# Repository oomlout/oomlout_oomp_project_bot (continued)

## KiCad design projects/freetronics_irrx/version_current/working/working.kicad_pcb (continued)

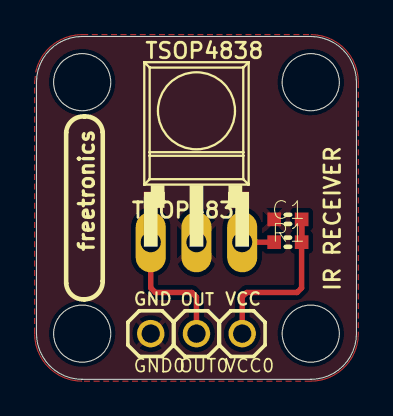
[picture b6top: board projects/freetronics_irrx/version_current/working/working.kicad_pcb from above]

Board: 2 copper layers, 17.8 x 19.0 mm, 10 parts (0 on the bottom side), 4 nets.

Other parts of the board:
@HOLE0, @HOLE1, @HOLE2, @HOLE3: (no value)

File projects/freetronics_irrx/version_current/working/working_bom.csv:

"Id";"Designator";"Footprint";"Quantity";"Designation";"Supplier and ref";
1;"R1";"0603";1;"100R";;;
2;"@HOLE3,@HOLE0,@HOLE1,@HOLE2";"";4;"";;;
3;"C1";"0603";1;"0.1u";;;
4;"VCC0,GND0,OUT0";"1X01";3;"M01PTH";;;
5;"TSOP4838";"TO220";1;"TSOP4838";;;

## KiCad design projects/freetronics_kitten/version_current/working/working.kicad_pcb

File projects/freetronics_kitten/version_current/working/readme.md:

# OOMP Project  
## KitTen  by freetronics  
  
oomp key: oomp_projects_flat_freetronics_kitten  
(snippet of original readme)  
  
Freetronics KitTen  
==================  
Copyright 2010-2013 Freetronics Pty Ltd    
Freetronics site:  www.freetronics.com    
Freetronics email: info@freetronics.com    
  
A fully-featured Arduino-compatible board in kit form. Includes a  
voltage regulator and extensive filtering, plus a prototyping area.  
  
Features:  
  
 * Prototyping area  
 * Overlay guide where you need it (both top and bottom)  
 * D13 pin works for everything thanks to FET isolation  
 * RX pin biased  
 * Mounting holes and power pads  
 * R3 (revision 3) Arduino header format  
  
More information is available at:  
  
  http://www.freetronics.com/kitten  

INSTALLATION  
------------  
The design is saved as an EAGLE project. EAGLE PCB design software is  
available from www.cadsoftusa.com free for non-commercial use. To use  
this project download it and place the directory containing these files  
into the "eagle" directory on your computer. Then open EAGLE and  
navigate to Projects -> eagle -> KitTen.  

DISTRIBUTION  
------------  
The specific terms of distribution of this project are governed by the  
license referenced below.  

LICENSE  
-------  
This work is licensed under the  
Creative Commons Attribution-Share Alike License.    
To view a copy of this license, visit  
  
  http://creativecommons.org/licenses/by-sa/3.0/    
  http://creativecommons.org/licenses/by-sa/3.0/legalcode  
  
or send a letter to  
  
  Creative Commons    
  171 Second Street, Suite 300    
  San Francisco    
  California, 94105    
  USA  
  
The "license" folder within this repository also c  
  full source readme at [readme_src.md](readme_src.md)  
  
source repo at: [https://github.com/freetronics/KitTen](https://github.com/freetronics/KitTen)  
## Board  

## Schematic  

[schematic pdf](working_schematic.pdf)  
## Images

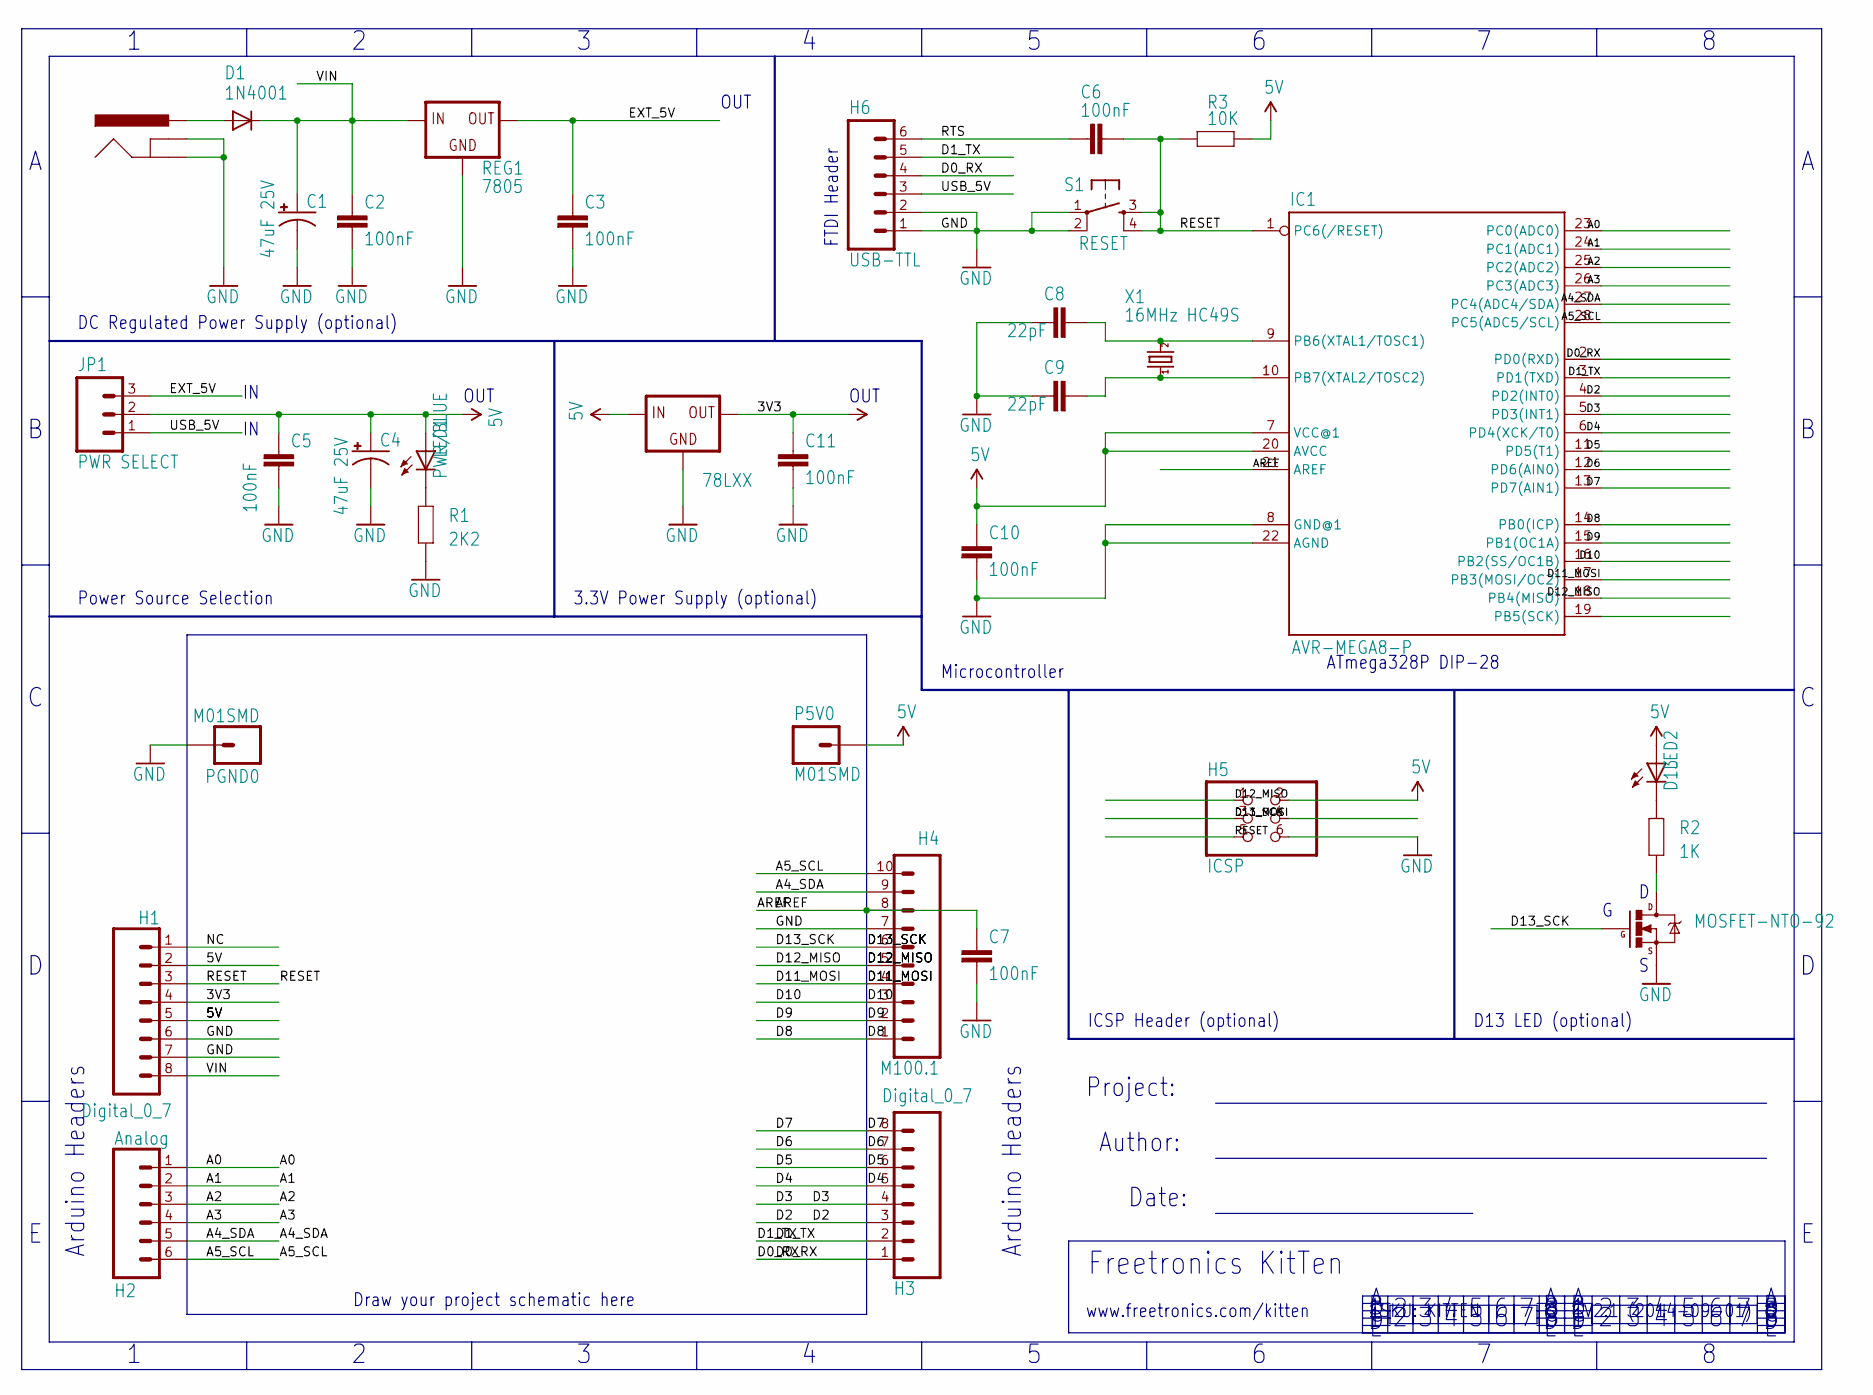
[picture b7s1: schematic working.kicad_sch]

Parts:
C1, C4: 47uF 25V; CPOL-RADIAL-10UF-25V
C2, C3, C5, C6, C7, C10, C11: 100nF; CAP-PTH-SMALL
C8, C9: 22pF; CAP-PTH-SMALL
D1: 1N4001; DIODE-1N4001
H1, H3: Digital_0_7; 1X08
H2: Analog; 1X06
H4: M100.1; 1X10
H5: ICSP; 2X03
H6: USB-TTL; 1X06
IC1: AVR-MEGA8-P; DIL28-3
JP1: PWR SELECT; 1X03
LED1: PWR/BLUE; LED3MM
LED2: D13; LED3MM
P5V0: M01SMD; LUXEON-PAD
PGND0: M01SMD; LUXEON-PAD
Q1: MOSFET-NTO-92; TO92
R1: 2K2; AXIAL-0.3
R2: 1K; AXIAL-0.3
R3: 10K; AXIAL-0.3
REG1: 7805; 78XXL
REG2: 78LXX; TO92
S1: RESET; TACTILE-PTH
SCK1: POWER_JACKPTH; POWER_JACK_PTH
X1: 16MHz HC49S; HC49U-V

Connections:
3V3: C11.1, H1.4, REG2.1 (OUT)
5V: C4.1 (+), C5.1, C10.1, H1.2, H1.5, H5.2, IC1.7 (VCC@1), IC1.20 (AVCC), JP1.2, LED1.A, LED2.A, P5V0.P$1, R3.P$2 (2), REG2.3 (IN)
A0: H2.1, IC1.23 (PC0(ADC0))
A1: H2.2, IC1.24 (PC1(ADC1))
A2: H2.3, IC1.25 (PC2(ADC2))
A3: H2.4, IC1.26 (PC3(ADC3))
A4_SDA: H2.5, H4.9, IC1.27 (PC4(ADC4/SDA))
A5_SCL: H2.6, H4.10, IC1.28 (PC5(ADC5/SCL))
AREF: C7.1, H4.8, IC1.21 (AREF)
D0_RX: H3.1, H6.4, IC1.2 (PD0(RXD))
D1_TX: H3.2, H6.5, IC1.3 (PD1(TXD))
D2: H3.3, IC1.4 (PD2(INT0))
D3: H3.4, IC1.5 (PD3(INT1))
D4: H3.5, IC1.6 (PD4(XCK/T0))
D5: H3.6, IC1.11 (PD5(T1))
D6: H3.7, IC1.12 (PD6(AIN0))
D7: H3.8, IC1.13 (PD7(AIN1))
D8: H4.1, IC1.14 (PB0(ICP))
D9: H4.2, IC1.15 (PB1(OC1A))
D10: H4.3, IC1.16 (PB2(SS/OC1B))
D11_MOSI: H4.4, H5.4, IC1.17 (PB3(MOSI/OC2))
D12_MISO: H4.5, H5.1, IC1.18 (PB4(MISO))
D13_SCK: H4.6, H5.3, IC1.19 (PB5(SCK)), Q1.2 (G)
EXT_5V: C3.1, JP1.3, REG1.OUT
GND: C1.2 (-), C2.2, C3.2, C4.2 (-), C5.2, C7.2, C8.1, C9.1, C10.2, C11.2, H1.6, H1.7, H4.7, H5.6, H6.1, H6.2, IC1.8 (GND@1), IC1.22 (AGND), PGND0.P$1, Q1.1 (S), R1.P$1 (1), REG1.GND, REG2.2 (GND), S1.1, S1.2, SCK1.GND, SCK1.GNDBREAK
unnamed: LED2.K (C), R2.P$2 (2)
unnamed: C8.2, IC1.9 (PB6(XTAL1/TOSC1)), X1.2
unnamed: Q1.3 (D), R2.P$1 (1)
unnamed: C9.2, IC1.10 (PB7(XTAL2/TOSC2)), X1.1
unnamed: D1.A, SCK1.PWR
unnamed: LED1.K (C), R1.P$2 (2)
NC: H1.1
RESET: C6.2, H1.3, H5.5, IC1.1 (PC6(/RESET)), R3.P$1 (1), S1.3, S1.4
RTS: C6.1, H6.6
USB_5V: H6.3, JP1.1
VIN: C1.1 (+), C2.1, D1.C, H1.8, REG1.IN

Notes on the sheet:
Power Source Selection
www.freetronics.com/kitten
3.3V Power Supply (optional)
OUT
Date:
Draw your project schematic here
Author:
Arduino Headers
Project:
SKU: KITTEN
DC Regulated Power Supply (optional)
D13 LED (optional)
ATmega328P DIP-28
ICSP Header (optional)
Microcontroller
Freetronics KitTen
FTDI Header
V2.1 (2014-09-01)

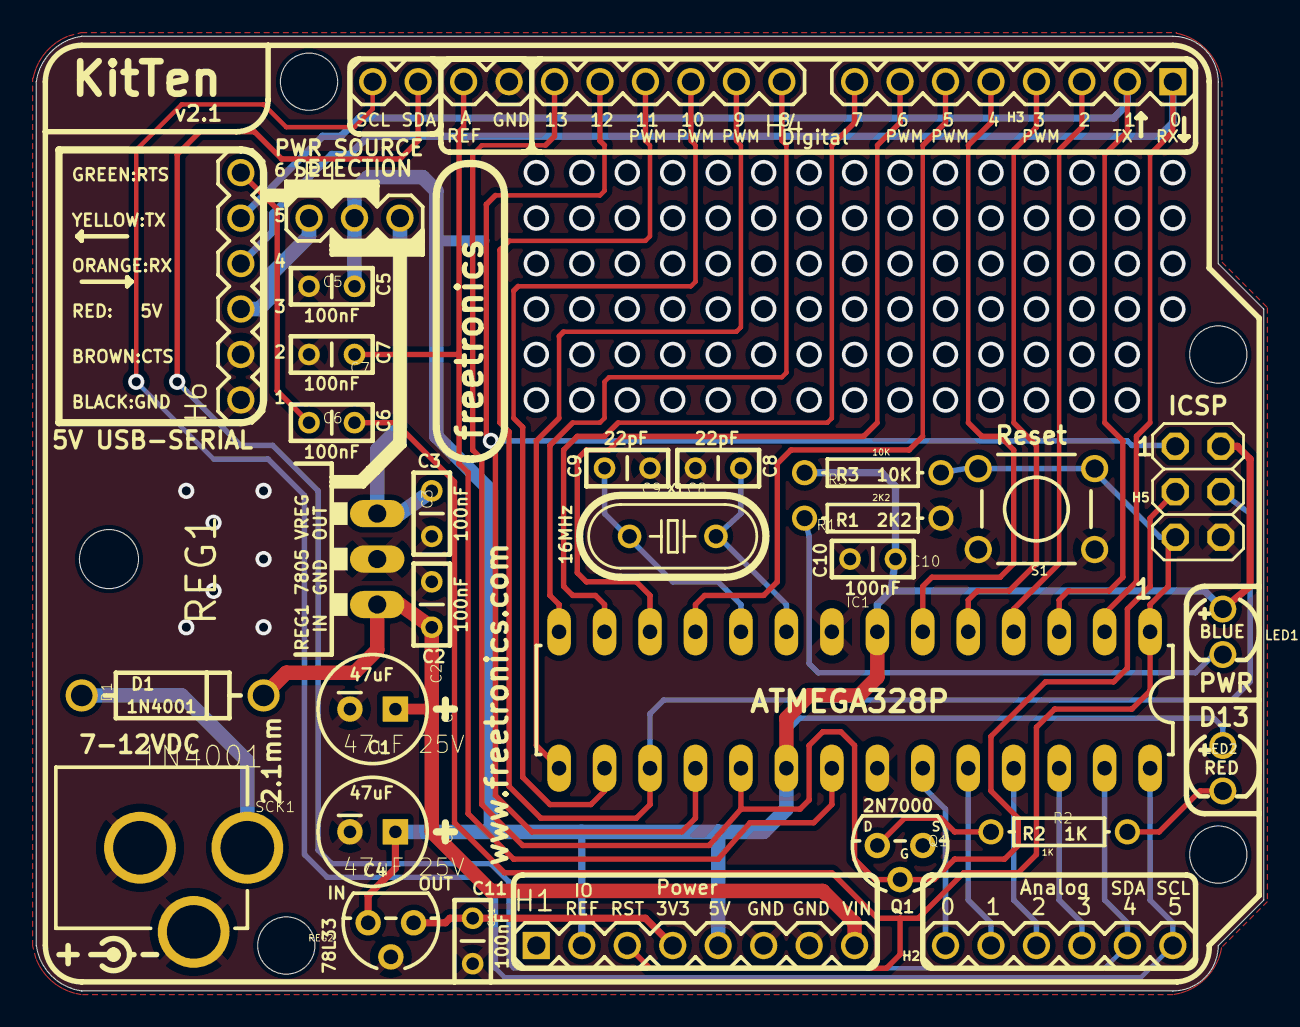
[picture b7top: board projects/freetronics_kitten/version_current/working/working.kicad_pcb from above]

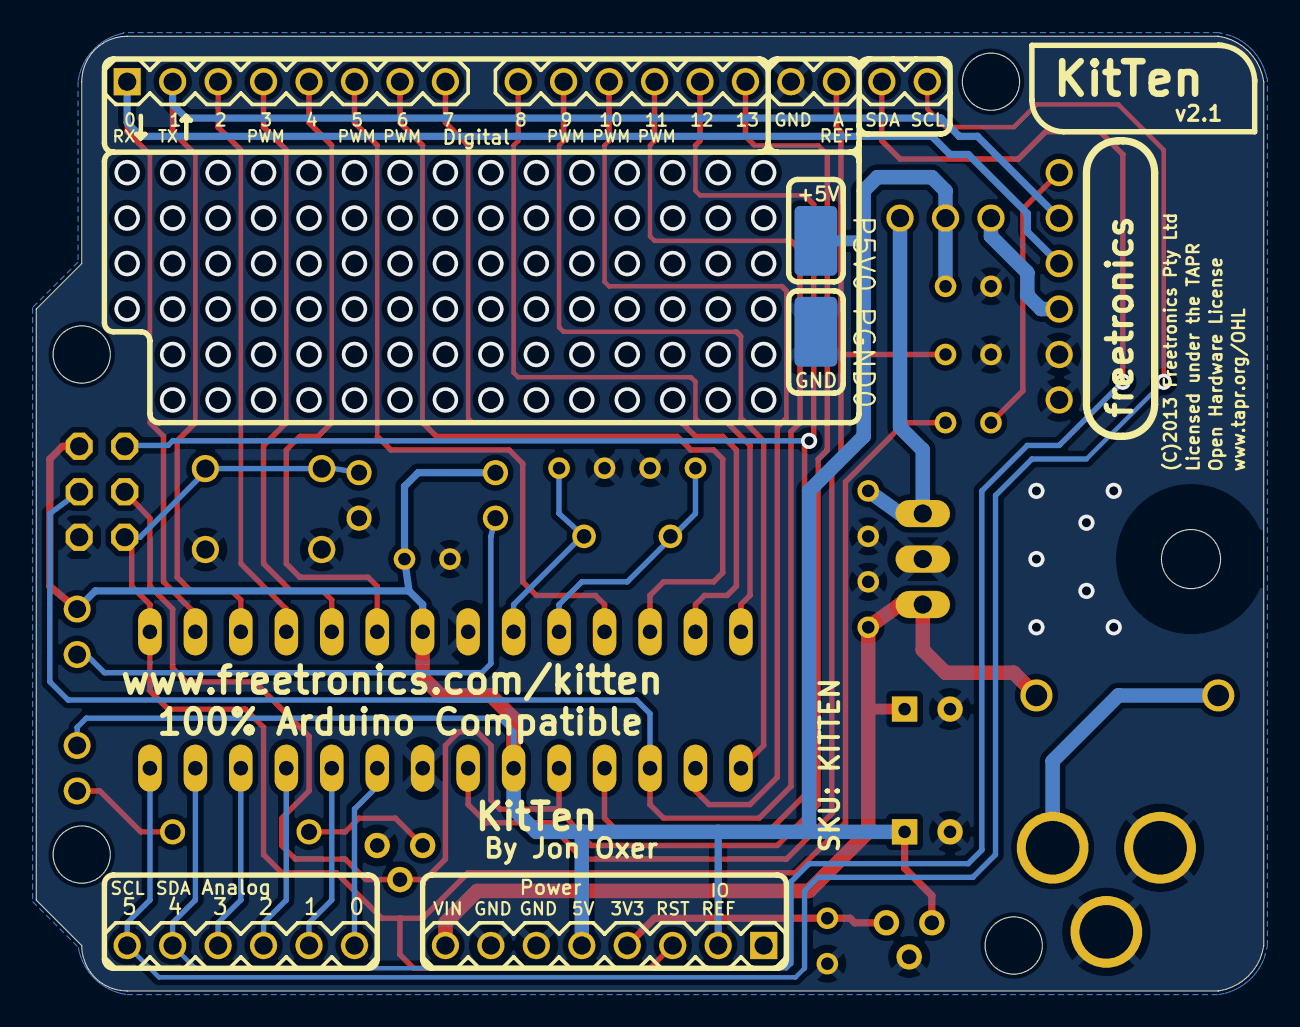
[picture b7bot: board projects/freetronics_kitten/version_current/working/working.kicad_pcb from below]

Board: 2 copper layers, 68.6 x 53.3 mm, 37 parts (2 on the bottom side), 35 nets.

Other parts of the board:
@HOLE0, @HOLE1, @HOLE2, @HOLE3: (no value)

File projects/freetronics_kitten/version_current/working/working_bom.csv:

"Id";"Designator";"Footprint";"Quantity";"Designation";"Supplier and ref";
1;"C3,C7,C6,C11,C5,C2,C10";"CAP-PTH-SMALL";7;"100nF";;;
2;"@HOLE3,@HOLE2,@HOLE1,@HOLE0";"";4;"";;;
3;"LED1";"LED3MM";1;"PWR/BLUE";;;
4;"JP1";"1X03";1;"PWR SELECT";;;
5;"S1";"TACTILE-PTH";1;"RESET";;;
6;"C8,C9";"CAP-PTH-SMALL";2;"22pF";;;
7;"H4";"1X10";1;"M100.1";;;
8;"H5";"2X03";1;"ICSP";;;
9;"H1,H3";"1X08";2;"Digital_0_7";;;
10;"C1,C4";"CPOL-RADIAL-10UF-25V";2;"47uF 25V";;;
11;"REG2";"TO92";1;"78L33";;;
12;"X1";"HC49U-V";1;"16MHz HC49S";;;
13;"R1";"AXIAL-0.3";1;"2K2";;;
14;"D1";"DIODE-1N4001";1;"1N4001";;;
15;"REG1";"78XXL";1;"7805";;;
16;"R2";"AXIAL-0.3";1;"1K";;;
17;"H2";"1X06";1;"Analog";;;
18;"IC1";"DIL28-3";1;"ATMEGA328P";;;
19;"SCK1";"POWER_JACK_PTH";1;"DC_2_1MM";;;
20;"H6";"1X06";1;"USB-TTL";;;
21;"R3";"AXIAL-0.3";1;"10K";;;
22;"Q1";"TO92";1;"2N7000";;;
23;"LED2";"LED3MM";1;"D13";;;
24;"P5V0,PGND0";"LUXEON-PAD";2;"";;;

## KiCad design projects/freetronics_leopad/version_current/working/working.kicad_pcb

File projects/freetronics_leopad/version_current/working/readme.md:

# OOMP Project  
## LEOPAD  by freetronics  
  
oomp key: oomp_projects_flat_freetronics_leopad  
(snippet of original readme)  
  
Freetronics LeoPad  
====================  
Copyright 2018 Freetronics Pty Ltd  www.freetronics.com    
  
A USB keypad with an ATMega32u4 controller, compatible with the Arduino  
Leonardo.  
  
Features:  
  
 * ATmega 32u4 MCU  
 * 20-key keypad (4x5 matrix)  
 * HWB (hardware boot) button and solder jumper to allow disabling bootloader  
 * 128x32 OLED module  
 * USB-C connector  
  
You can view more details at:  
  
  http://www.freetronics.com.au/leopad  

INSTALLATION  
------------  
The design is saved as an EAGLE project. EAGLE PCB design software is  
available from www.cadsoftusa.com free for non-commercial use. To use  
this project download it and place the directory containing these files  
into the "eagle" directory on your computer. Then open EAGLE and  
navigate to the project.  

CREDITS  
-------  
Jonathan Oxer jon@freetronics.com  

DISTRIBUTION  
------------  
The specific terms of distribution of this project are governed by the  
license referenced below.  

LICENSE  
-------  
Licensed under the TAPR Open Hardware License (www.tapr.org/OHL).  
The "license" folder within this repository also contains a copy of  
this license in plain text format.  
  
  full source readme at [readme_src.md](readme_src.md)  
  
source repo at: [https://github.com/freetronics/LEOPAD](https://github.com/freetronics/LEOPAD)  
## Board  

## Schematic  

[schematic pdf](working_schematic.pdf)  
## Images

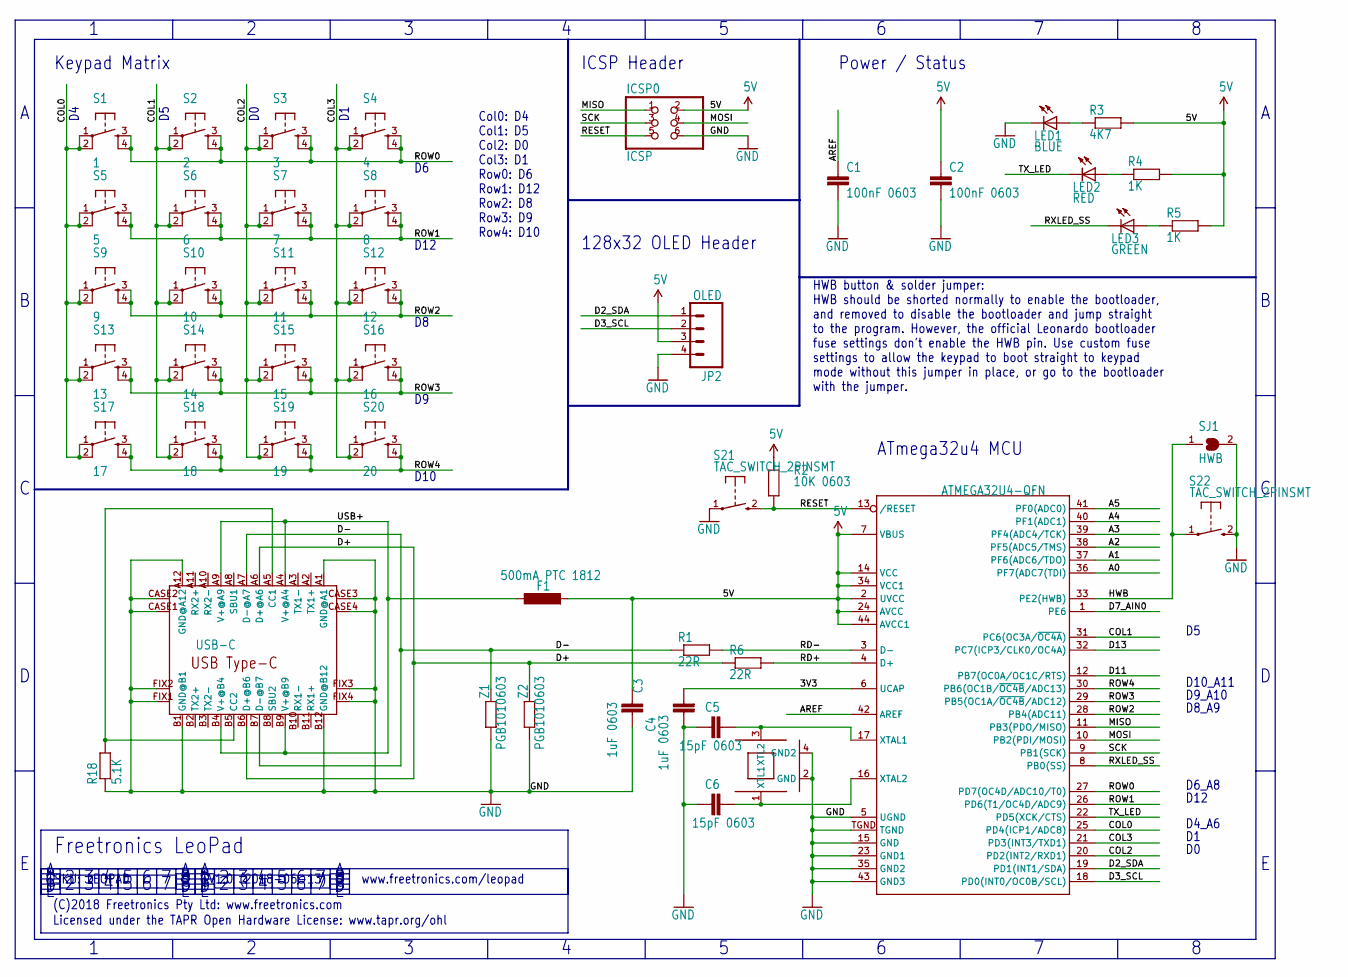
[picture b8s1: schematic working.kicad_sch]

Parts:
C1, C2: 100nF 0603; 0603
C3, C4: 1uF 0603; 0603
C5, C6: 15pF 0603; 0603
F1: 500mA PTC 1812; L1812
IC1: ATMEGA32U4-QFN; QFN-44N
ICSP0: ICSP; 2X03
JP2: OLED; 1X04
LED1: BLUE; LED-0603
LED2: RED; LED-0603
LED3: GREEN; LED-0603
R1, R6: 22R; 0603
R2: 10K 0603; 0603
R3: 4K7; 0603
R4, R5: 1K; 0603
R18: 5.1K; 0603
S1: 1; TACTILE-PTH-12MM
S2: 2; TACTILE-PTH-12MM
S3: 3; TACTILE-PTH-12MM
S4: 4; TACTILE-PTH-12MM
S5: 5; TACTILE-PTH-12MM
S6: 6; TACTILE-PTH-12MM
S7: 7; TACTILE-PTH-12MM
S8: 8; TACTILE-PTH-12MM
S9: 9; TACTILE-PTH-12MM
S10: 10; TACTILE-PTH-12MM
S11: 11; TACTILE-PTH-12MM
S12: 12; TACTILE-PTH-12MM
S13: 13; TACTILE-PTH-12MM
S14: 14; TACTILE-PTH-12MM
S15: 15; TACTILE-PTH-12MM
S16: 16; TACTILE-PTH-12MM
S17: 17; TACTILE-PTH-12MM
S18: 18; TACTILE-PTH-12MM
S19: 19; TACTILE-PTH-12MM
S20: 20; TACTILE-PTH-12MM
S21, S22: TAC_SWITCH_2PINSMT; TACTILE_SWITCH_SMD_2PIN_TINY
SJ1: HWB; SJ
U$15: USB-C; USB-C-U52A
XTL1: CRYSTAL-GND3X2; CRYSTAL-SMD-3X2
Z1, Z2: PGB1010603; 0603

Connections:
3V3: C4.2, IC1.6 (UCAP)
5V: C2.1, C3.1, F1.2, IC1.2 (UVCC), IC1.7 (VBUS), IC1.14 (VCC), IC1.24 (AVCC), IC1.34 (VCC1), IC1.44 (AVCC1), ICSP0.2, JP2.3, R2.2, R3.2, R4.2, R5.2
A0: IC1.36 (PF7(ADC7(TDI))
A1: IC1.37 (PF6(ADC6/TDO))
A2: IC1.38 (PF5(ADC5/TMS))
A3: IC1.39 (PF4(ADC4/TCK))
A4: IC1.40 (PF1(ADC1))
A5: IC1.41 (PF0(ADC0))
AREF: C1.1, IC1.42 (AREF)
COL0: IC1.25 (PD4(ICP1/ADC8)), S1.1, S1.2, S5.1, S5.2, S9.1, S9.2, S13.1, S13.2, S17.1, S17.2
COL1: IC1.31 (PC6(OC3A/~OC4A)), S2.1, S2.2, S6.1, S6.2, S10.1, S10.2, S14.1, S14.2, S18.1, S18.2
COL2: IC1.20 (PD2(INT2/RXD1)), S3.1, S3.2, S7.1, S7.2, S11.1, S11.2, S15.1, S15.2, S19.1, S19.2
COL3: IC1.21 (PD3(INT3/TXD1)), S4.1, S4.2, S8.1, S8.2, S12.1, S12.2, S16.1, S16.2, S20.1, S20.2
D2_SDA: IC1.19 (PD1(INT1/SDA)), JP2.1
D3_SCL: IC1.18 (PD0(INT0/OC0B/SCL)), JP2.2
D7_AIN0: IC1.1 (PE6)
D11: IC1.12 (PB7(OC0A/OC1C/RTS))
D13: IC1.32 (PC7(ICP3/CLK0/OC4A))
D+: R6.1, U$15.A6 (D+@A6), U$15.B6 (D+@B6), Z2.2
D-: R1.1, U$15.A7 (D-@A7), U$15.B7 (D-@B7), Z1.2
GND: C1.2, C2.2, C3.2, C4.1, C5.1, C6.1, IC1.5 (UGND), IC1.15 (GND), IC1.23 (GND1), IC1.35 (GND2), IC1.43 (GND3), IC1.TGND, ICSP0.6, JP2.4, LED1.C, R18.1, S21.1, S22.2 (S), SJ1.2, U$15.A1 (GND@A1), U$15.A12 (GND@A12), U$15.B1 (GND@B1), U$15.B12 (GND@B12), U$15.CASE1 (GND@CASE1), U$15.CASE2 (GND@CASE2), U$15.CASE3 (GND@CASE3), U$15.CASE4 (GND@CASE4), U$15.FIX1 (GND@FIX1), U$15.FIX2 (GND@FIX2), U$15.FIX3 (GND@FIX3), U$15.FIX4 (GND@FIX4), XTL1.2 (GND), XTL1.4 (GND2), Z1.1, Z2.1
HWB: IC1.33 (PE2(HWB)), S22.1, SJ1.1
MISO: IC1.11 (PB3(PDO/MISO)), ICSP0.1
MOSI: IC1.10 (PB2(PDI/MOSI)), ICSP0.4
unnamed: LED1.A, R3.1
unnamed: LED2.A, R4.1
unnamed: LED3.A, R5.1
unnamed: C5.2, IC1.17 (XTAL1), XTL1.3 (XTL2)
unnamed: C6.2, IC1.16 (XTAL2), XTL1.1 (XTL1)
unnamed: R18.2, U$15.A5 (CC1), U$15.B5 (CC2)
RD+: IC1.4 (D+), R6.2
RD-: IC1.3 (D-), R1.2
RESET: IC1.13 (/RESET), ICSP0.5, R2.1, S21.2 (S)
ROW0: IC1.27 (PD7(OC4D/ADC10/T0)), S1.3, S1.4, S2.3, S2.4, S3.3, S3.4, S4.3, S4.4
ROW1: IC1.26 (PD6(T1/OC4D/ADC9)), S5.3, S5.4, S6.3, S6.4, S7.3, S7.4, S8.3, S8.4
ROW2: IC1.28 (PB4(ADC11)), S9.3, S9.4, S10.3, S10.4, S11.3, S11.4, S12.3, S12.4
ROW3: IC1.29 (PB5(OC1A/~OC4B/ADC12)), S13.3, S13.4, S14.3, S14.4, S15.3, S15.4, S16.3, S16.4
ROW4: IC1.30 (PB6(OC1B/~OC4B/ADC13)), S17.3, S17.4, S18.3, S18.4, S19.3, S19.4, S20.3, S20.4
RXLED_SS: IC1.8 (PB0(SS)), LED3.C
SCK: IC1.9 (PB1(SCK)), ICSP0.3
TX_LED: IC1.22 (PD5(XCK/CTS)), LED2.C
USB+: F1.1, U$15.A4 (V+@A4), U$15.A9 (V+@A9), U$15.B4 (V+@B4), U$15.B9 (V+@B9)

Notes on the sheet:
D10_A11
D4_A6
Keypad Matrix
ATmega32u4 MCU
Col0: D4 Col1: D5 Col2: D0 Col3: D1 Row0: D6 Row1: D12 Row2: D8 Row3: D9 Row4: D10
Freetronics LeoPad
D9_A10
ICSP Header
Licensed under the TAPR Open Hardware License: www.tapr.org/ohl
128x32 OLED Header
V1.0 (2018-06-13)
D12
D6_A8
Power / Status
SKU: LEOPAD
(C)2018 Freetronics Pty Ltd: www.freetronics.com
D10
www.freetronics.com/leopad
D8_A9
HWB button & solder jumper: HWB should be shorted normally to enable the bootloader, and removed to disable the bootloader and jump straight to the program. However, the official Leonardo bootloader fuse settings don't enable the HWB pin. Use custom fuse settings to allow the keypad to boot straigh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

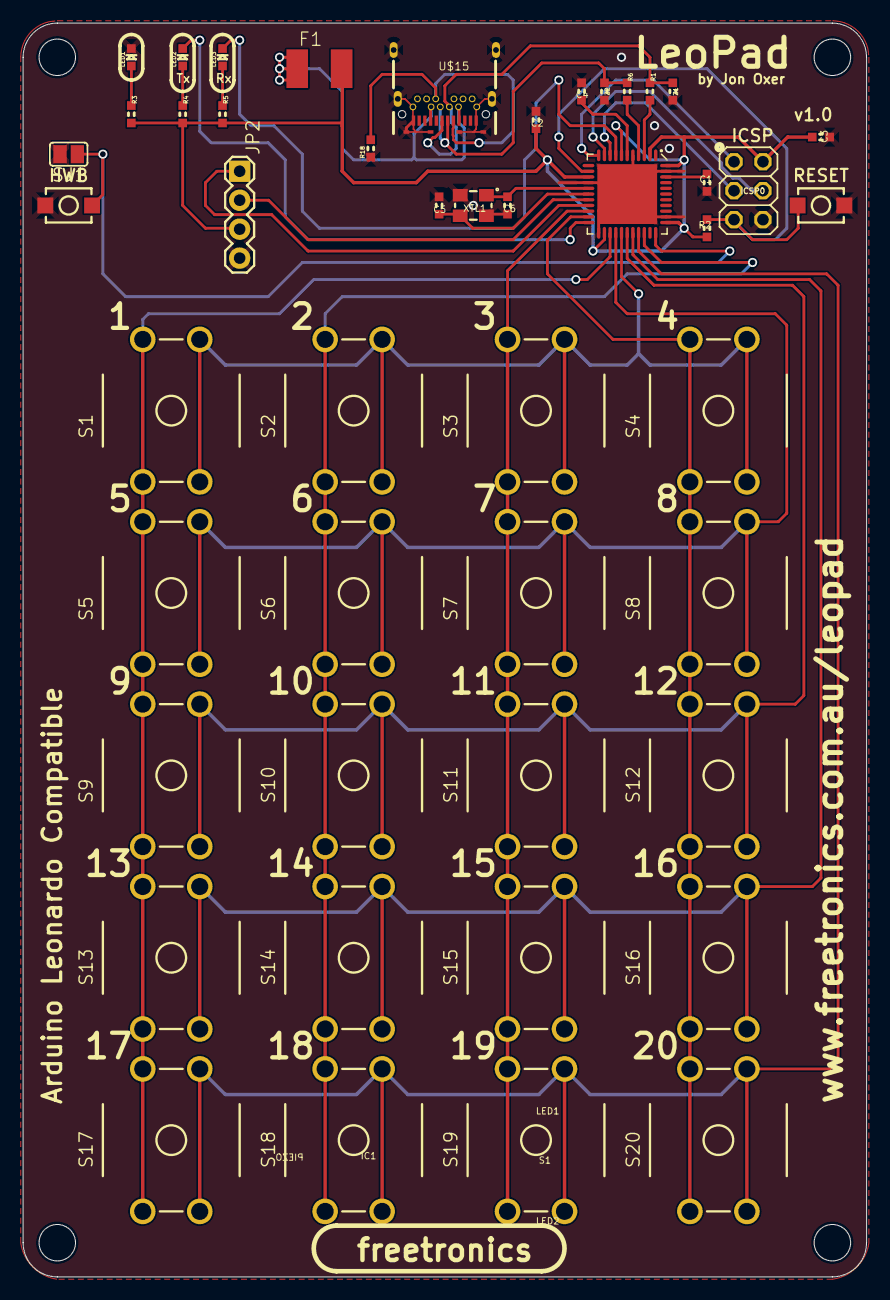
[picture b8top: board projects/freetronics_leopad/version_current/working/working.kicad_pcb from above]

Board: 2 copper layers, 74.0 x 110.0 mm, 51 parts (0 on the bottom side), 33 nets.

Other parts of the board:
@HOLE0, @HOLE1, @HOLE2, @HOLE3: (no value)

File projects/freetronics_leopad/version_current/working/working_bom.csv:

"Id";"Designator";"Footprint";"Quantity";"Designation";"Supplier and ref";
1;"S13";"TACTILE-PTH-12MM";1;"13";;;
2;"S4";"TACTILE-PTH-12MM";1;"4";;;
3;"JP2";"1X04";1;"OLED";;;
4;"R18";"0603";1;"5.1K";;;
5;"XTL1";"CRYSTAL-SMD-3X2";1;"16MHz";;;
6;"R2";"0603";1;"10K 0603";;;
7;"S10";"TACTILE-PTH-12MM";1;"10";;;
8;"S12";"TACTILE-PTH-12MM";1;"12";;;
9;"C3,C4";"0603";2;"1uF 0603";;;
10;"LED1";"LED-0603";1;"BLUE";;;
11;"Z1,Z2";"0603";2;"PGB1010603";;;
12;"S19";"TACTILE-PTH-12MM";1;"19";;;
13;"C6,C5";"0603";2;"15pF 0603";;;
14;"S7";"TACTILE-PTH-12MM";1;"7";;;
15;"S8";"TACTILE-PTH-12MM";1;"8";;;
16;"S18";"TACTILE-PTH-12MM";1;"18";;;
17;"R5,R4";"0603";2;"1K";;;
18;"S17";"TACTILE-PTH-12MM";1;"17";;;
19;"S22";"TACTILE_SWITCH_SMD_2PIN_TINY";1;"HWB";;;
20;"S20";"TACTILE-PTH-12MM";1;"20";;;
21;"S11";"TACTILE-PTH-12MM";1;"11";;;
22;"S1";"TACTILE-PTH-12MM";1;"1";;;
23;"@HOLE2,@HOLE0,@HOLE1,@HOLE3";"";4;"";;;
24;"C2,C1";"0603";2;"100nF 0603";;;
25;"F1";"L1812";1;"500mA PTC 1812";;;
26;"S3";"TACTILE-PTH-12MM";1;"3";;;
27;"S14";"TACTILE-PTH-12MM";1;"14";;;
28;"R3";"0603";1;"4K7";;;
29;"IC1";"QFN-44N";1;"ATMEGA32U4-QFN";;;
30;"S15";"TACTILE-PTH-12MM";1;"15";;;
31;"SJ1";"SJ";1;"HWB";;;
32;"R6,R1";"0603";2;"22R";;;
33;"U$15";"USB-C-U52A";1;"USB-C";;;
34;"S9";"TACTILE-PTH-12MM";1;"9";;;
35;"S16";"TACTILE-PTH-12MM";1;"16";;;
36;"S2";"TACTILE-PTH-12MM";1;"2";;;
37;"S5";"TACTILE-PTH-12MM";1;"5";;;
38;"LED3";"LED-0603";1;"GREEN";;;
39;"ICSP0";"2X03";1;"ICSP";;;
40;"S6";"TACTILE-PTH-12MM";1;"6";;;
41;"LED2";"LED-0603";1;"RED";;;
42;"S21";"TACTILE_SWITCH_SMD_2PIN_TINY";1;"RESET";;;
